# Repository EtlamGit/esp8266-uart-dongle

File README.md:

# esp8266-uart-dongle

A project for an esp8266 dongle for various IoT projects using UART.

Several manufacturers of home devices like air condition use a modified USB
connector as so called Wifi-Module to bring the devices into the manufacurer
cloud. These dongles can be replaced by this project to control your device
in your own cloud.

This project is inspired by https://github.com/dudanov/iot-uni-dongle

As there are no KiCad project files available, I had to rebuild it from scratch.

Other similar projects are:
* https://github.com/ezcGman/mideahvac-dongle

## Main goals

Stay the same as in the original project from Dudanov:

* using popular Wi-Fi module [ESP12-F](https://docs.ai-thinker.com/_media/esp8266/docs/esp-12f_product_specification_en.pdf) based on ESP8266 SoC
* unified design for all types of home devices from different manufacturers
* use of various connectors with a pitch of 2.54 mm and USB
* possibility of swapping the middle signal TX/RX contacts
* IR transmission and receiving via one wire connected to TSOP output
* very small design: PCB size 24.75 x 19 mm

I extended this with my own ideas:

* use only components in JLCPCB Basic or Promotional library
* use AMS1117 LDO
* use 0805 SMD components to allow hand soldering
* add reset pull-up and reset button
* add 100nF capacitor for ESP supply

## SMT assembly at JLCPCB

The [gerber](gerber) directory contains the files necessary for manufacturing
and assembling the board at the [JLCPCB](https://jlcpcb.com) factory.

You may get a warning notice that the USB connector is not present, but that
is intended as you have to solder that manually only when you need it.

Further steps are soldering the ESP module and selecting the TX/RX pin via
solder jumpers.

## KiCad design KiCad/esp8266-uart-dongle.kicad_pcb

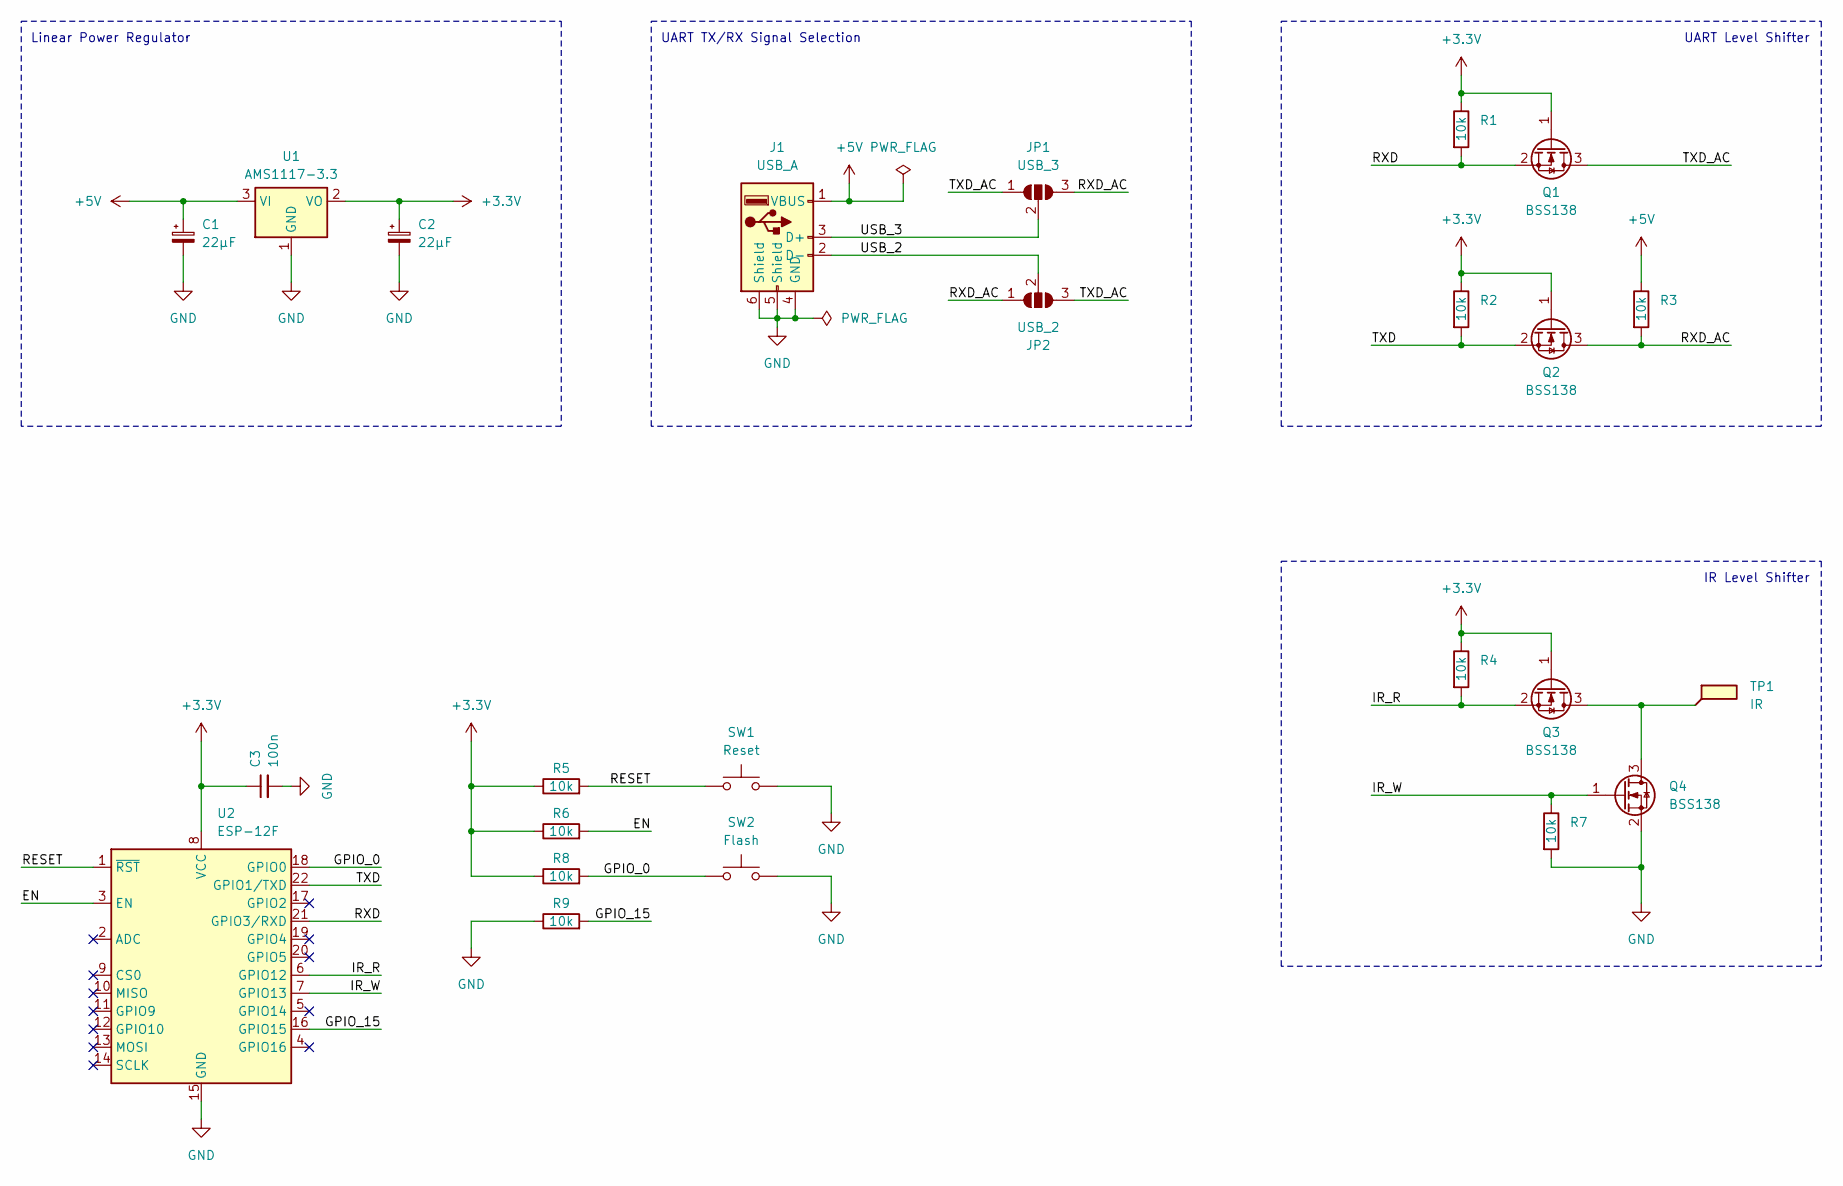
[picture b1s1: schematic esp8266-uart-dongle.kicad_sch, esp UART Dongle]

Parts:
C1, C2: 22µF; C_0805_2012Metric_Pad1.18x1.45mm_HandSolder; LCSC Part # C45783
C3: 100n; C_0805_2012Metric; LCSC Part # C49678
J1: USB_A; USB-A-TH_USB-ZL-109PWB
JP1: USB_3; SolderJumper-3_P1.3mm_Open_RoundedPad1.0x1.5mm_NumberLabels
JP2: USB_2; SolderJumper-3_P1.3mm_Open_RoundedPad1.0x1.5mm_NumberLabels
Q1, Q2, Q3, Q4: BSS138; SOT-23; LCSC Part # C7420339
R1, R2, R3, R4, R5, R6, R7, R8, R9: 10k; R_0805_2012Metric_Pad1.20x1.40mm_HandSolder; LCSC Part # C17414
SW1: Reset; SW_SPST_TS-1088-xR020; LCSC Part # C720477
SW2: Flash; SW_SPST_TS-1088-xR020; LCSC Part # C720477
TP1: IR; TestPoint_Keystone_5019_Miniature
U1: AMS1117-3.3; SOT-223-3_TabPin2; LCSC Part # C6186
U2: ESP-12F; ESP-12E; LCSC Part # C82891

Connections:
+3.3V: C2.1, C3.1, Q1.1 (G), Q2.1 (G), Q3.1 (G), R1.1, R2.1, R4.1, R5.1, R6.1, R8.1, U1.2 (VO), U2.8 (VCC)
+5V: C1.1, J1.1 (VBUS), R3.1, U1.3 (VI)
/EN: R6.2, U2.3 (EN)
/GPIO_0: R8.2, SW2.1, U2.18 (GPIO0)
/GPIO_15: R9.2, U2.16 (GPIO15)
/IR_R: Q3.2 (S), R4.2, U2.6 (GPIO12)
/IR_W: Q4.1 (G), R7.1, U2.7 (GPIO13)
/RESET: R5.2, SW1.1, U2.1 (~RST)
/RXD: Q1.2 (S), R1.2, U2.21 (GPIO3/RXD)
/RXD_AC: JP1.3 (B), JP2.1 (A), Q2.3 (D), R3.2
/TXD: Q2.2 (S), R2.2, U2.22 (GPIO1/TXD)
/TXD_AC: JP1.1 (A), JP2.3 (B), Q1.3 (D)
/USB_2: J1.2 (D-), JP2.2 (C)
/USB_3: J1.3 (D+), JP1.2 (C)
GND: C1.2, C2.2, C3.2, J1.4 (GND), J1.5 (Shield), J1.6 (Shield), Q4.2 (S), R7.2, R9.1, SW1.2, SW2.2, U1.1 (GND), U2.15 (GND)
unnamed: Q3.3 (D), Q4.3 (D), TP1.1 (1_1)

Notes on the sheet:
UART TX/RX Signal Selection
UART Level Shifter
IR Level Shifter
Linear Power Regulator

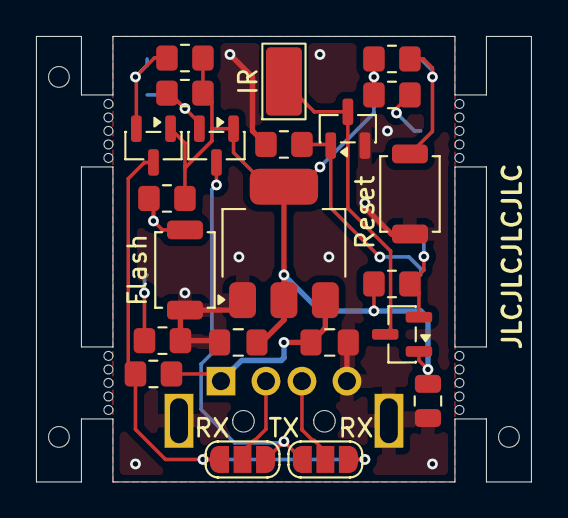
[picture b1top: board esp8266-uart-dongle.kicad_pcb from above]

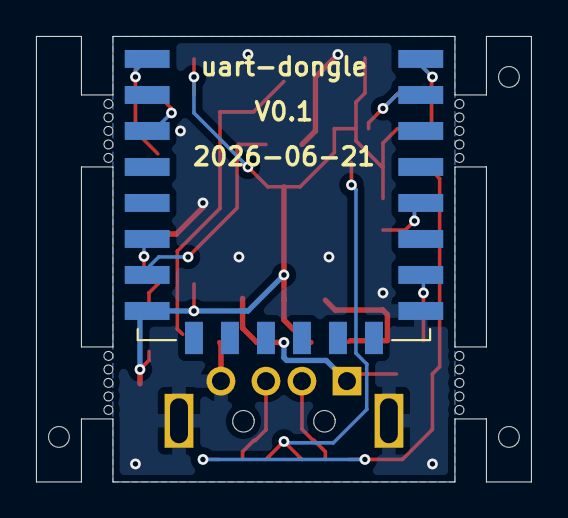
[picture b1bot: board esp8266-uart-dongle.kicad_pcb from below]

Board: 2 copper layers, 27.5 x 24.8 mm, 24 parts (2 on the bottom side), 16 nets.

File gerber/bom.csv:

"Reference","LCSC Part #","Qty","Value","DNP","Exclude from BOM","Exclude from Board","Footprint","Datasheet"
"C1,C2","C45783","2","22µF","","","","Capacitor_SMD:C_0805_2012Metric_Pad1.18x1.45mm_HandSolder",""
"C3","C49678","1","100n","","","","Capacitor_SMD:C_0805_2012Metric",""
"Q1,Q2,Q3,Q4","C7420339","4","BSS138","","","","Package_TO_SOT_SMD:SOT-23","https://www.onsemi.com/pub/Collateral/BSS138-D.PDF"
"R1,R2,R3,R4,R5,R6,R7,R8,R9","C17414","9","10k","","","","Resistor_SMD:R_0805_2012Metric_Pad1.20x1.40mm_HandSolder",""
"SW1","C720477","1","Reset","","","","Button_Switch_SMD:SW_SPST_TS-1088-xR020",""
"SW2","C720477","1","Flash","","","","Button_Switch_SMD:SW_SPST_TS-1088-xR020",""
"U1","C6186","1","AMS1117-3.3","","","","Package_TO_SOT_SMD:SOT-223-3_TabPin2","http://www.advanced-monolithic.com/pdf/ds1117.pdf"
"U2","C82891","1","ESP-12F","","","","RF_Module:ESP-12E","http://wiki.ai-thinker.com/_media/esp8266/esp8266_series_mod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"

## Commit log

2026-06-25 initial commit for V0.1
